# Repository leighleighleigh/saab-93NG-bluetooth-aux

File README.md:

# saab-93NG-bluetooth-aux
A module to augment the Aux-In functionality of SAAB 93NG's (2002/3+), to add Bluetooth media playback and steering wheel media control support.

<blockquote>
<p><b>September 30th 2022 update - PCB ordered!</b></p>

</blockquote>

# Features
 - Bluetooth music playback through the wired AUX port
 - Steering wheel button controls
   - Play / Pause
   - Next / Previous
   - *WIP* Voice Assistant 
   - *WIP* Accept incoming phone call 
 - **[SOON]** Digital Microphone support
 - **[FUTURE]** SID integration for automatic Aux-switching
 - **[FUTURE]** SID augmentation, to show music track names etc.

# Project Layout
- /hardware/saab_bluetooth_aux_kit
  - Version 1 hardware. Very basic, breakout-module-based. KiCAD 5
- /hardware/saab_bluetooth_aux_kit_v2
  - Version 2 of the 'kit'. WeMos LOLIN32-Lite module is used as the MCU. Some SMD components for power supply and CAN. Multiple through-hole DAC options (PCM5102, UDH1334H). KiCAD 6.
- /hardware/esp32_93NG_btaux_v2
  - Version 2 hardware, unfinished. Intention was to use full-SMD components, and have multiple CAN interfaces. Currently too much work, and not as approachable for newbies.
- /esp32_a2dp_reciever
  - PlatformIO project, the software flashed to the ESP32 module.
  - Utilises the Arduino for ESP32 framework.

# Version 1, Prototype
The first edition of the PCB serves only to wire together some off-the-shelf modules, after they were tested on a breadboard.

## Prototype parts
 - ESP32 NodeMCU Board (30-pin variant)
 - Adafruit I2S to Stereo DAC (UDA1334)
 - MCP2515 CAN-bus to SPI interface module

<!-- 
# Notes for building your own (by [jokubasver](https://github.com/jokubasver))
- CAN H connects to LS GMLAN1 (green wire, it can be found on the ICM connector pin 1, or solder directly to ICM connector PCB pad).
- CAN L connects to GND
- Connect a 4.7k resistor between CAN H and CAN L
  - So to make it simple - Since the whole Bluetooth Aux board is getting GND from the AUX connection, I connected GND from the MCP2515 module to CAN L, and I connected a 4.7k resistor across CAN H and CAN L on the MCP2515 module.

- Everything also works if I leave CAN L disconnected and not use the 4.7k resistor. CAN L can be left floating as described here: https://electronics.stackexchange.com/questions/139562/single-wire-can-saab-9-3-i-bus-gmlan#comment670941_139882
  - Question is - which is the proper way? Leave out the terminating resistor and leave CAN L floating? Or connect CAN L to GND and use a 4.7k terminating resistor? Both connection variants seem to work fine.

- Instead of using 12V, the EHU 5V line can be used.
  - It turns off after ~10-15 seconds after locking the car with the remote. 
  - 5V wakes up as soon as you unlock the car.
  - This requires the use of an isolated 5V-5V DC-DC converter (see below)

- 5V, GND, AUX Left, AUX right can be soldered on the EHU PCB. All pads are clearly marked.

- Using EHU 5V will cause some audible Bluetooth interference. 
  - Use an isolated 5V-5V DC-DC converter to eliminate it (CC3-0505SF-E would be pin-compatible and would fit nicely on the bluetooth aux kit PCB)
  - I am personally using AM1SS-0505SJZ together with capacitors and inductors that are shown in the datasheet's example schematic. 

- **Warning on EHU 5V line**
  - I have experienced massive current draw from the battery when using this 5V line previously, while experimenting with a generic Bluetooth Aux module. I tried it again with this project and everything is fine.
  - My guess is that my first experiment had a ground loop, and this either caused current to flow through the ground loop, draining the battery, or it confused the EHU and prevented it to go into sleep.
  - Therefore, I highly suggest you use an isolated DC-DC converter (whether you are using 12V, or 5V from the EHU)
-->

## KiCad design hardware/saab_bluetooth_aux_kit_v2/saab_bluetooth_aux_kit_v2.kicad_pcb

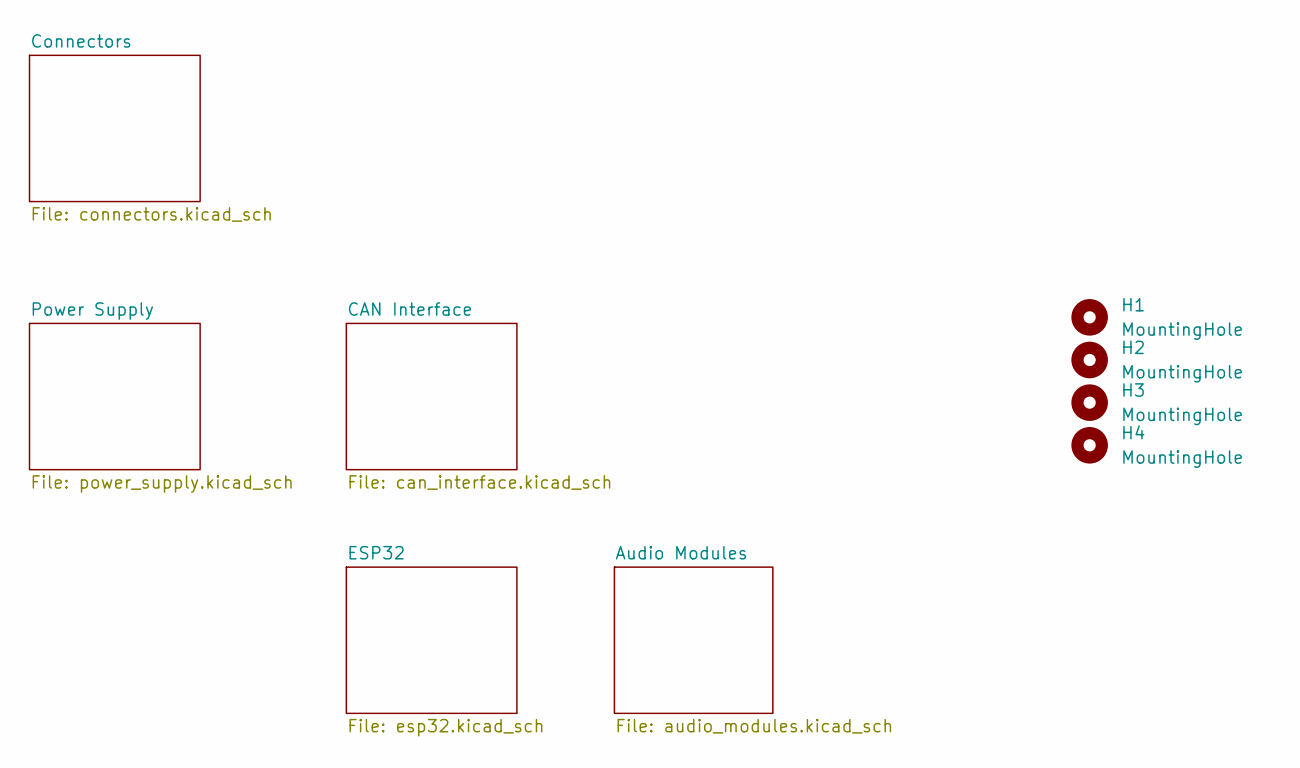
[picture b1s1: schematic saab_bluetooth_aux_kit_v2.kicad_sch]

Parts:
H1, H2, H3, H4: MountingHole; MountingHole_3.2mm_M3_BARE

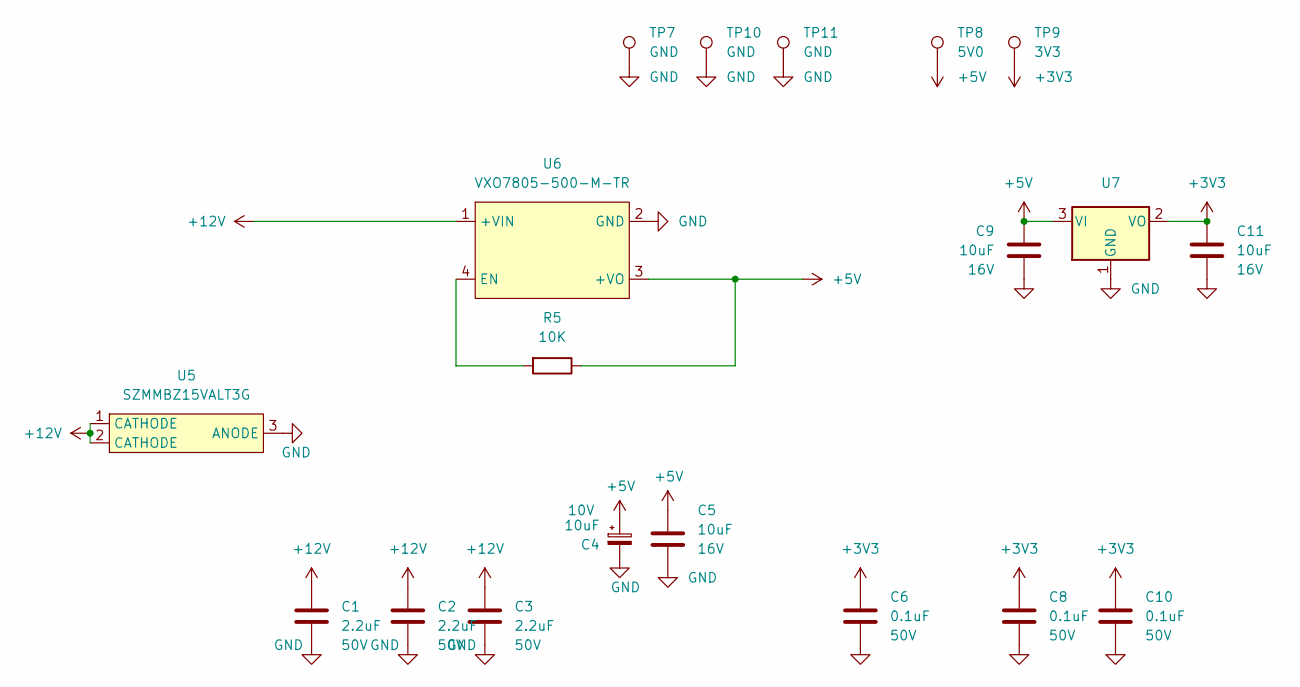
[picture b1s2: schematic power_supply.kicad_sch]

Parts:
C1, C2, C3: 2.2uF; C_0805_2012Metric; Rated Voltage 50V
C4: 10uF; CP_EIA-6032-20_AVX-F; Voltage 10V
C5, C9, C11: 10uF; C_0805_2012Metric; Rated Voltage 16V
C6, C8, C10: 0.1uF; C_0805_2012Metric; Rated Voltage 50V
R5: 10K; R_0805_2012Metric
TP7, TP10, TP11: GND; TestPoint_THTPad_D2.0mm_Drill1.0mm
TP8: 5V0; TestPoint_THTPad_D2.0mm_Drill1.0mm
TP9: 3V3; TestPoint_THTPad_D2.0mm_Drill1.0mm
U5: SZMMBZ15VALT3G; TSOT-23
U6: VXO7805-500-M-TR
U7: NCP1117LPST33T3G; SOT-223-3_TabPin2

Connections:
+3V3: C6.1, C8.1, C10.1, C11.1, TP9.1, U7.2 (VO); also elsewhere on the board
+5V: C4.1, C5.1, C9.1, R5.1, TP8.1, U6.3 (+VO), U7.3 (VI); also elsewhere on the board
+12V: C1.1, C2.1, C3.1, U5.1 (CATHODE), U5.2 (CATHODE), U6.1 (+VIN); also elsewhere on the board
GND: C1.2, C2.2, C3.2, C4.2, C5.2, C6.2, C8.2, C9.2, C10.2, C11.2, TP7.1, TP10.1, TP11.1, U5.3 (ANODE), U6.2 (GND), U7.1 (GND); also elsewhere on the board
unnamed: R5.2, U6.4 (EN)

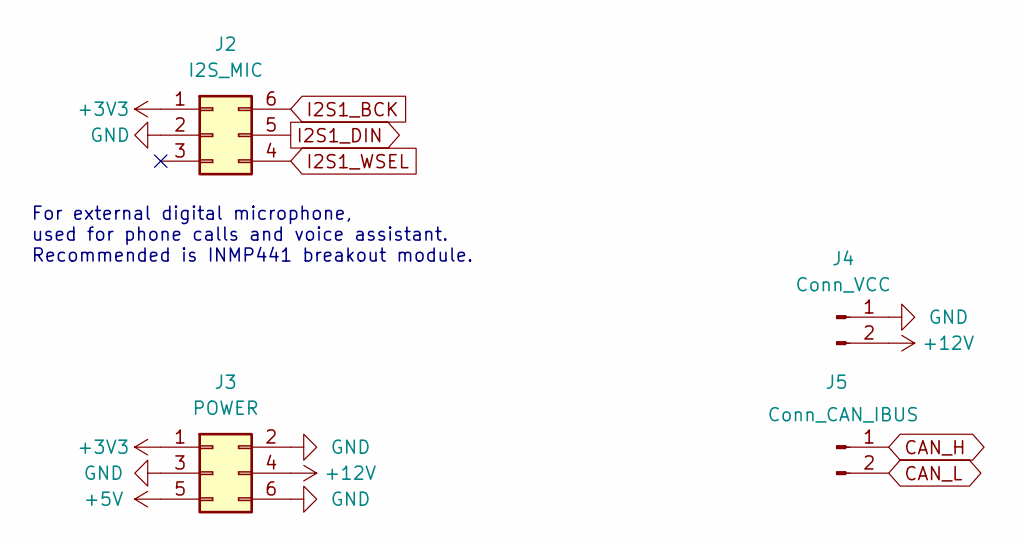
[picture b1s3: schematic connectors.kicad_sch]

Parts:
J2: I2S_MIC; PinHeader_2x03_P2.54mm_Vertical
J3: POWER; PinHeader_2x03_P2.54mm_Vertical
J4: Conn_VCC; Molex_Mega-Fit_76825-0002_2x01_P5.70mm_Horizontal
J5: Conn_CAN_IBUS; Molex_Mega-Fit_76825-0002_2x01_P5.70mm_Horizontal

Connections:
+3V3: J2.1, J3.1; also elsewhere on the board
+5V: J3.5; also elsewhere on the board
+12V: J3.4, J4.2; also elsewhere on the board
CAN_H: J5.1; also elsewhere on the board
CAN_L: J5.2; also elsewhere on the board
GND: J2.2, J3.2, J3.3, J3.6, J4.1; also elsewhere on the board
I2S1_BCK: J2.6; also elsewhere on the board
I2S1_DIN: J2.5; also elsewhere on the board
I2S1_WSEL: J2.4; also elsewhere on the board

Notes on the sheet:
For external digital microphone, used for phone calls and voice assistant. Recommended is INMP441 breakout module.

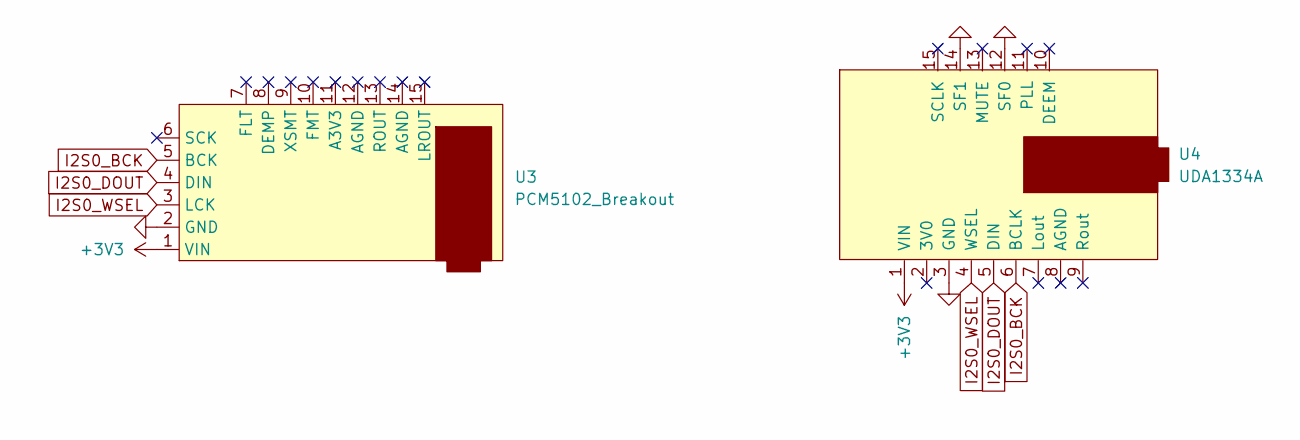
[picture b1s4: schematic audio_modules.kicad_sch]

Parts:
U3: PCM5102_Breakout
U4: UDA1334A; UDA1334_AudioBreakout

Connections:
+3V3: U3.1 (VIN), U4.1 (VIN); also elsewhere on the board
GND: U3.2 (GND), U4.3 (GND), U4.12 (SF0), U4.14 (SF1); also elsewhere on the board
I2S0_BCK: U3.5 (BCK), U4.6 (BCLK); also elsewhere on the board
I2S0_DOUT: U3.4 (DIN), U4.5 (DIN); also elsewhere on the board
I2S0_WSEL: U3.3 (LCK), U4.4 (WSEL); also elsewhere on the board

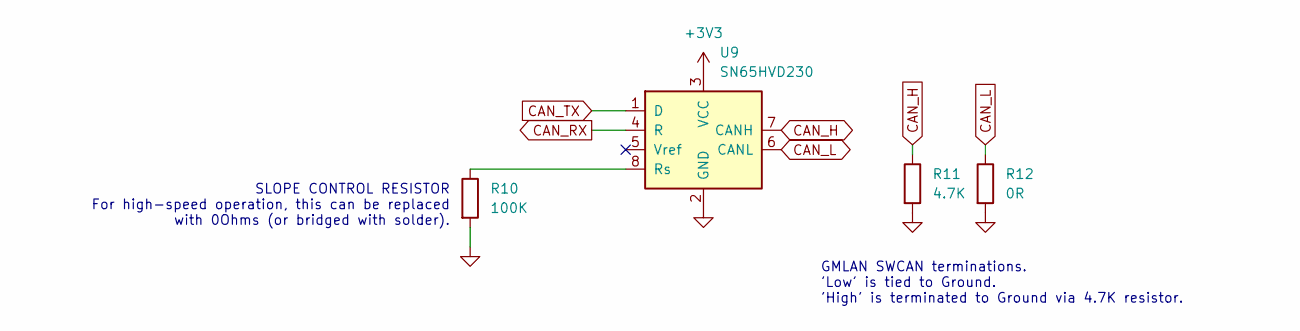
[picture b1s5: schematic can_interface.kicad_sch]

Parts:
R10: 100K; R_0805_2012Metric
R11: 4.7K; R_1206_3216Metric
R12: 0R; R_1206_3216Metric
U9: SN65HVD230; SOIC-8_3.9x4.9mm_P1.27mm

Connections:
+3V3: U9.3 (VCC); also elsewhere on the board
CAN_H: R11.1, U9.7 (CANH); also elsewhere on the board
CAN_L: R12.1, U9.6 (CANL); also elsewhere on the board
CAN_RX: U9.4 (R); also elsewhere on the board
CAN_TX: U9.1 (D); also elsewhere on the board
GND: R10.2, R11.2, R12.2, U9.2 (GND); also elsewhere on the board
unnamed: R10.1, U9.8 (Rs)

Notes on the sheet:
SLOPE CONTROL RESISTOR For high-speed operation, this can be replaced with 0Ohms (or bridged with solder).
GMLAN SWCAN terminations. 'Low' is tied to Ground. 'High' is terminated to Ground via 4.7K resistor.

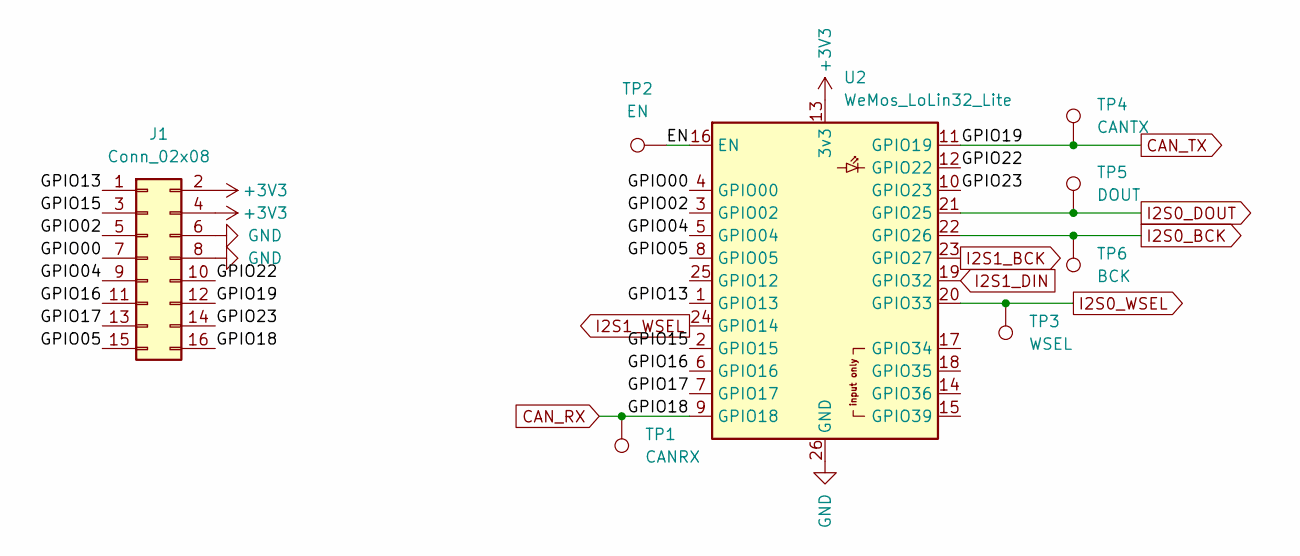
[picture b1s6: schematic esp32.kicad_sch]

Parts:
J1: Conn_02x08; PinHeader_2x08_P2.54mm_Vertical
TP1: CANRX; TestPoint_THTPad_D2.0mm_Drill1.0mm
TP2: EN; TestPoint_THTPad_D2.0mm_Drill1.0mm
TP3: WSEL; TestPoint_THTPad_D2.0mm_Drill1.0mm
TP4: CANTX; TestPoint_THTPad_D2.0mm_Drill1.0mm
TP5: DOUT; TestPoint_THTPad_D2.0mm_Drill1.0mm
TP6: BCK; TestPoint_THTPad_D2.0mm_Drill1.0mm
U2: WeMos_LoLin32_Lite; WEMOS_LoLin32_Lite

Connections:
+3V3: J1.2, J1.4, U2.13 (3v3); also elsewhere on the board
/ESP32/EN: TP2.1, U2.16 (EN)
/ESP32/GPIO00: J1.7, U2.4 (GPIO00)
/ESP32/GPIO02: J1.5, U2.3 (GPIO02)
/ESP32/GPIO04: J1.9, U2.5 (GPIO04)
/ESP32/GPIO05: J1.15, U2.8 (GPIO05)
/ESP32/GPIO13: J1.1, U2.1 (GPIO13)
/ESP32/GPIO15: J1.3, U2.2 (GPIO15)
/ESP32/GPIO16: J1.11, U2.6 (GPIO16)
/ESP32/GPIO17: J1.13, U2.7 (GPIO17)
/ESP32/GPIO22: J1.10, U2.12 (GPIO22)
/ESP32/GPIO23: J1.14, U2.10 (GPIO23)
CAN_RX: J1.16, TP1.1, U2.9 (GPIO18); also elsewhere on the board
CAN_TX: J1.12, TP4.1, U2.11 (GPIO19); also elsewhere on the board
GND: J1.6, J1.8, U2.26 (GND); also elsewhere on the board
I2S0_BCK: TP6.1, U2.22 (GPIO26); also elsewhere on the board
I2S0_DOUT: TP5.1, U2.21 (GPIO25); also elsewhere on the board
I2S0_WSEL: TP3.1, U2.20 (GPIO33); also elsewhere on the board
I2S1_BCK: U2.23 (GPIO27); also elsewhere on the board
I2S1_DIN: U2.19 (GPIO32); also elsewhere on the board
I2S1_WSEL: U2.24 (GPIO14); also elsewhere on the board

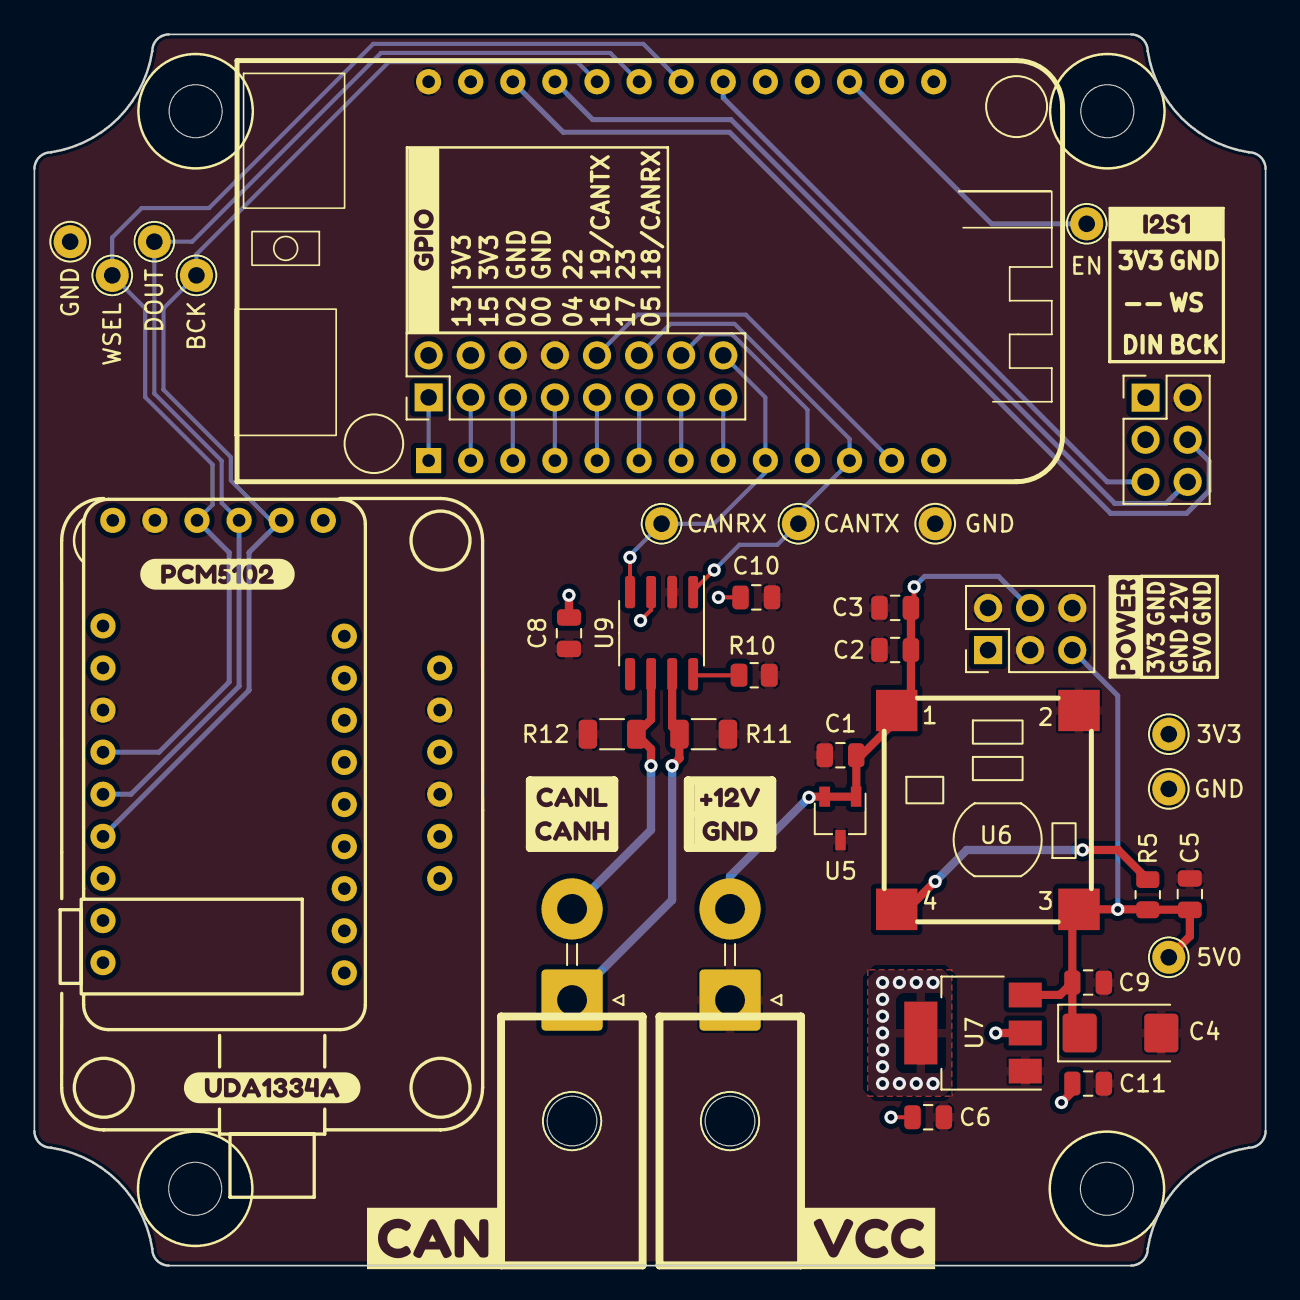
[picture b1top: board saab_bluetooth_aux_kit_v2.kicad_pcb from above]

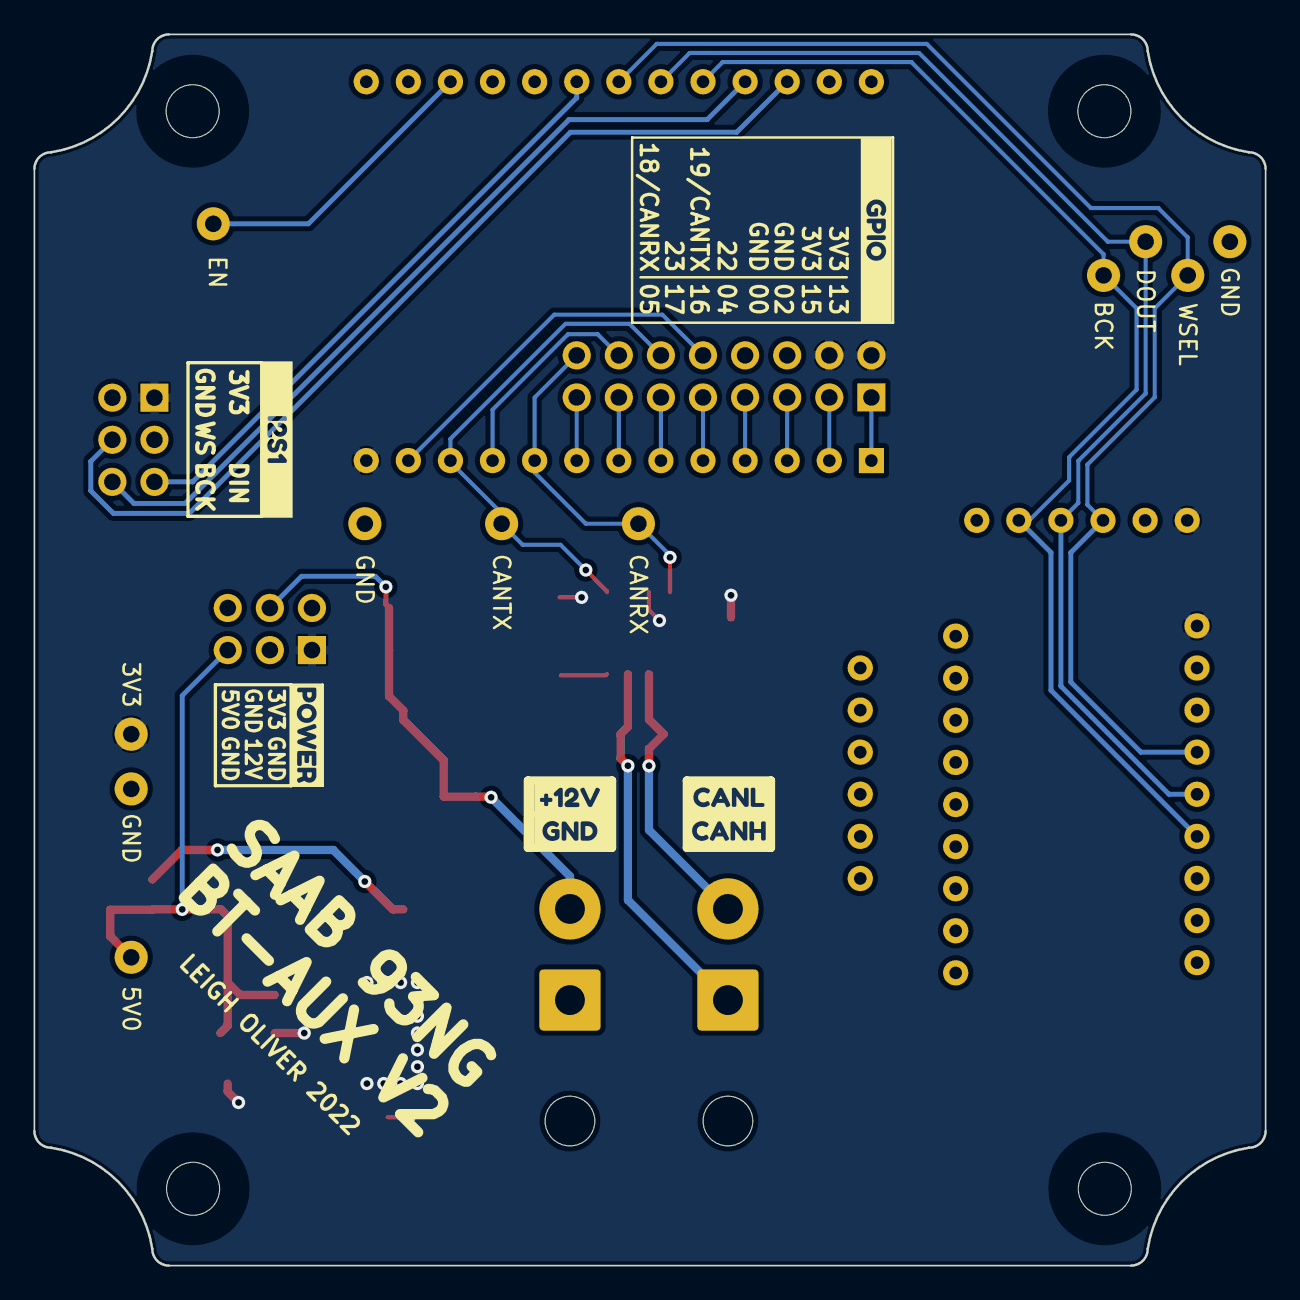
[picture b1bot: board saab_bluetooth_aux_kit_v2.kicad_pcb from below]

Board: 2 copper layers, 74.3 x 74.3 mm, 59 parts (7 on the bottom side), 27 nets.

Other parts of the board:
kibuzzard-62F392E4: G***; kibuzzard-62F392E4
kibuzzard-62F3934B: G***; kibuzzard-62F3934B
kibuzzard-632C5E36: G***; kibuzzard-632C5E36
kibuzzard-632C5EA9: G***; kibuzzard-632C5EA9
kibuzzard-632C5EB0: G***; kibuzzard-632C5EB0
kibuzzard-632C431C, kibuzzard-632C431C#2: G***; kibuzzard-632C431C
kibuzzard-632C4321, kibuzzard-632C4321#2: G***; kibuzzard-632C4321
kibuzzard-632C4325, kibuzzard-632C4325#2: G***; kibuzzard-632C4325
kibuzzard-632C4329, kibuzzard-632C4329#2: G***; kibuzzard-632C4329
kibuzzard-632C7032, kibuzzard-632C7032#2: G***; kibuzzard-632C7032
kibuzzard-632F06BD, kibuzzard-632F06BD#2: G***; kibuzzard-632F06BD
kibuzzard-632F14FF: G***; kibuzzard-632F14FF

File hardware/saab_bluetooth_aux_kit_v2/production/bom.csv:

Designator,Footprint,Quantity,Value,LCSC Part #
TP7,TestPoint_THTPad_D2.0mm_Drill1.0mm,1,GND,
C5,C_0805_2012Metric,1,10uF,
TP9,TestPoint_THTPad_D2.0mm_Drill1.0mm,1,3V3,
TP11,TestPoint_THTPad_D2.0mm_Drill1.0mm,1,GND,
R5,R_0805_2012Metric,1,10K,
R10,R_0805_2012Metric,1,100K,
C10,C_0805_2012Metric,1,0.1uF,
H1,MountingHole_3.2mm_M3_BARE,1,MountingHole,
U6,VXO7805-500-M-TR,1,VXO7805-500-M-TR,
U4,UDA1334_AudioBreakout,1,UDA1334A,
H4,MountingHole_3.2mm_M3_BARE,1,MountingHole,
TP6,TestPoint_THTPad_D2.0mm_Drill1.0mm,1,BCK,
TP10,TestPoint_THTPad_D2.0mm_Drill1.0mm,1,GND,
TP3,TestPoint_THTPad_D2.0mm_Drill1.0mm,1,WSEL,
C4,CP_EIA-6032-20_AVX-F,1,10uF,
TP4,TestPoint_THTPad_D2.0mm_Drill1.0mm,1,CANTX,
TP8,TestPoint_THTPad_D2.0mm_Drill1.0mm,1,5V0,
R12,R_1206_3216Metric,1,0R,
H3,MountingHole_3.2mm_M3_BARE,1,MountingHole,
C8,C_0805_2012Metric,1,0.1uF,
TP5,TestPoint_THTPad_D2.0mm_Drill1.0mm,1,DOUT,
C3,C_0805_2012Metric,1,2.2uF,
U9,SOIC-8_3.9x4.9mm_P1.27mm,1,SN65HVD230,
C1,C_0805_2012Metric,1,2.2uF,
TP2,TestPoint_THTPad_D2.0mm_Drill1.0mm,1,EN,
J3,PinHeader_2x03_P2.54mm_Vertical,1,POWER,
J4,Molex_Mega-Fit_76825-0002_2x01_P5.70mm_Horizontal,1,Conn_VCC,
C11,C_0805_2012Metric,1,10uF,
U3,PCM5102_Breakout,1,PCM5102_Breakout,
TP1,TestPoint_THTPad_D2.0mm_Drill1.0mm,1,CANRX,
H2,MountingHole_3.2mm_M3_BARE,1,MountingHole,
U2,WEMOS_LoLin32_Lite,1,WeMos_LoLin32_Lite,
C6,C_0805_2012Metric,1,0.1uF,
U7,SOT-223-3_TabPin2,1,NCP1117LPST33T3G,
J2,PinHeader_2x03_P2.54mm_Vertical,1,I2S_MIC,
U5,TSOT-23,1,SZMMBZ15VALT3G,
C2,C_0805_2012Metric,1,2.2uF,
R11,R_1206_3216Metric,1,4.7K,
C9,C_0805_2012Metric,1,10uF,
J1,PinHeader_2x08_P2.54mm_Vertical,1,Conn_02x08,
J5,Molex_Mega-Fit_76825-0002_2x01_P5.70mm_Horizontal,1,Conn_CAN_IBUS,

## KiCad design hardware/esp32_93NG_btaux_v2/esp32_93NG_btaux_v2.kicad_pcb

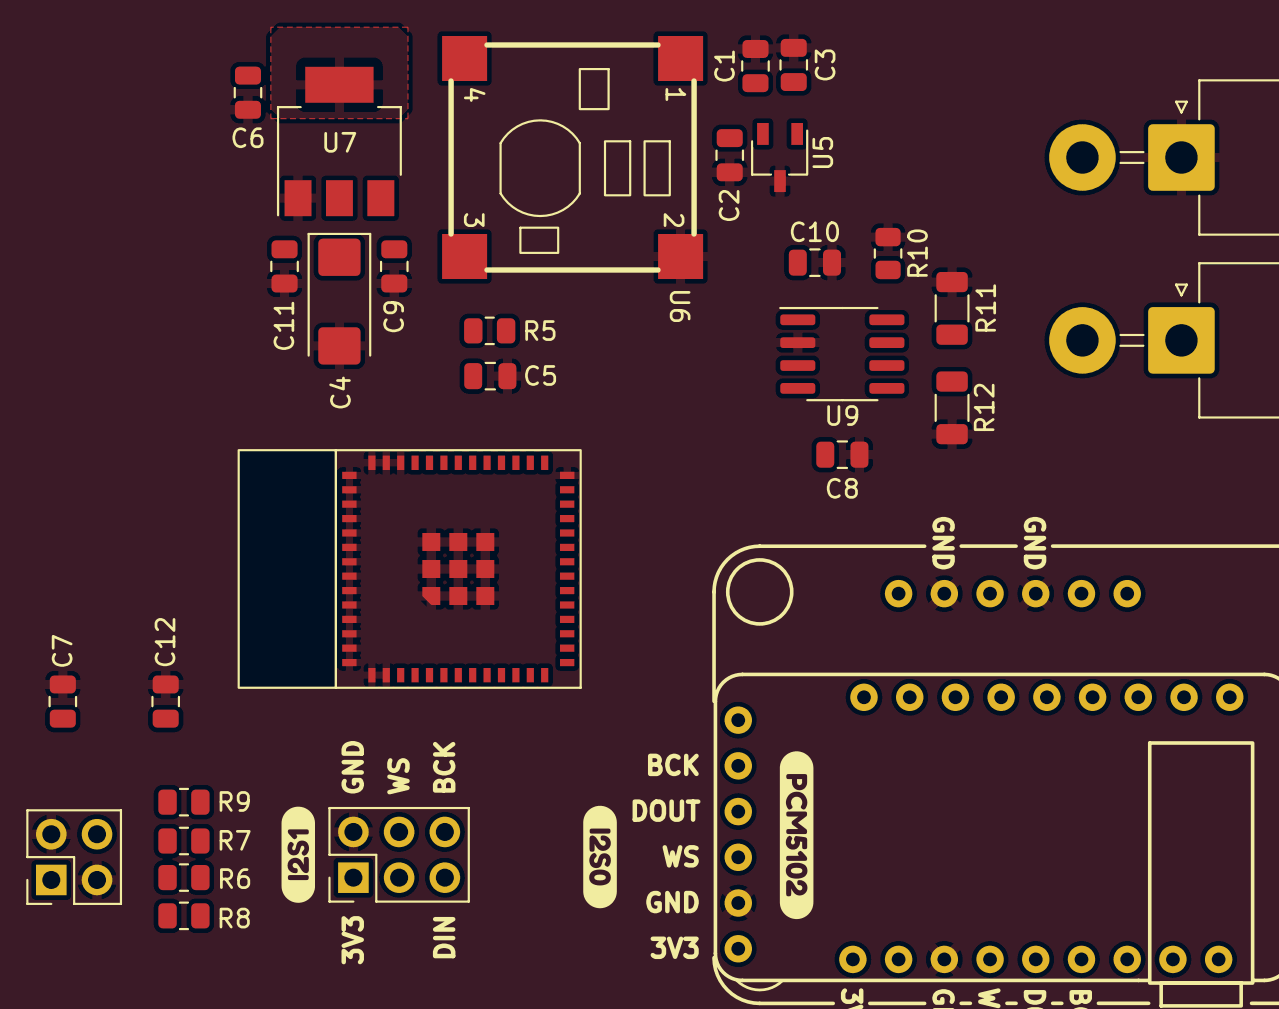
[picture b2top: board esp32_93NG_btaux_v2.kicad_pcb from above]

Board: 2 copper layers, 40 parts (1 on the bottom side), 20 nets, no tracks yet.

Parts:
C1, C2, C3: 2.2uF; C_0805_2012Metric
C4: 10uF; CP_EIA-6032-20_AVX-F
C5, C9, C11, C12: 10uF; C_0805_2012Metric
C6, C7, C8, C10: 0.1uF; C_0805_2012Metric
H1, H2, H3, H4: MountingHole; MountingHole_3.2mm_M3_BARE
J1: SW_EXT; PinHeader_2x02_P2.54mm_Vertical
J2: I2S_MIC; PinHeader_2x03_P2.54mm_Vertical
J4: Conn_VCC; Molex_Mega-Fit_76825-0002_2x01_P5.70mm_Horizontal
J5: Conn_CAN_IBUS; Molex_Mega-Fit_76825-0002_2x01_P5.70mm_Horizontal
R5: 10K; R_0805_2012Metric
R6, R7: 470; R_0805_2012Metric
R8, R9: 10k; R_0805_2012Metric
R10: 100K; R_0805_2012Metric
R11: 4.7K; R_1206_3216Metric
R12: 0R; R_1206_3216Metric
U3: PCM5102_Breakout
U4: UDA1334A; UDA1334_AudioBreakout
U5: SZMMBZ15VALT3G; TSOT-23
U6: VXO7805-500-M-TR
U7: NCP1117LPST33T3G; SOT-223-3_TabPin2
U8: ESP32-MINI-1
U9: SN65HVD230; SOIC-8_3.9x4.9mm_P1.27mm
kibuzzard-62F392E4: G***; kibuzzard-62F392E4
kibuzzard-62F394C5, kibuzzard-62F394C5#2: G***; kibuzzard-62F394C5
kibuzzard-62F395A5: G***; kibuzzard-62F395A5
kibuzzard-62F3934B: G***; kibuzzard-62F3934B

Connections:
+3V3: C6.1, C7.1, C8.1, C10.1, C11.1, C12.1, J2.1, R8.1, R9.1, U3.1 (VIN), U4.1 (VIN), U7.2 (VO), U8.3 (3V3), U9.3 (VCC)
+5V: C4.1, C5.1, C9.1, R5.1, U6.3 (+VO), U7.3 (VI)
+12V: C1.1, C2.1, C3.1, J4.2, U5.1 (CATHODE), U5.2 (CATHODE), U6.1 (+VIN)
/ESP32/BOOT_SW: J1.4, R7.2
/ESP32/EN_SW: J1.1, R6.2
CAN_H: J5.1, R11.1, U9.7 (CANH)
CAN_L: J5.2, R12.1, U9.6 (CANL)
CAN_RX: U8.30 (IO18), U9.4 (R)
CAN_TX: U8.32 (IO19), U9.1 (D)
EN: R6.1, R8.2, U8.8 (EN)
GND: C1.2, C2.2, C3.2, C4.2, C5.2, C6.2, C7.2, C8.2, C9.2, C10.2, C11.2, C12.2, J1.2, J1.3, J2.2, J4.1, R10.2, R11.2, R12.2, U3.2 (GND), U4.3 (GND), U4.12 (SF0), U4.14 (SF1), U5.3 (ANODE), U6.2 (GND), U7.1 (GND), U8.1 (GND), U8.2 (GND), U8.27 (GND), U8.38 (GND), U8.39 (GND), U8.40 (GND), U8.41 (GND), U8.42 (GND), U8.43 (GND), U8.44 (GND), U8.45 (GND), U8.46 (GND), U8.47 (GND), U8.48 (GND), U8.49 (GND), U8.50 (GND), U8.51 (GND), U8.52 (GND), U8.53 (GND), U8.54 (GND), U8.55 (EPAD), U9.2 (GND)
I2S0_BCK: U3.5 (BCK), U4.6 (BCLK), U8.14 (IO26)
I2S0_DOUT: U3.4 (DIN), U4.5 (DIN), U8.13 (IO25)
I2S0_WSEL: U3.3 (LCK), U4.4 (WSEL), U8.12 (IO33)
I2S1_BCK: J2.6, U8.15 (IO27)
I2S1_DIN: J2.5, U8.11 (IO32)
I2S1_WSEL: J2.4, U8.16 (IO14)
IO0: R7.1, R9.2, U8.21 (IO0)
unnamed: R5.2, U6.4 (EN)
unnamed: R10.1, U9.8 (Rs)

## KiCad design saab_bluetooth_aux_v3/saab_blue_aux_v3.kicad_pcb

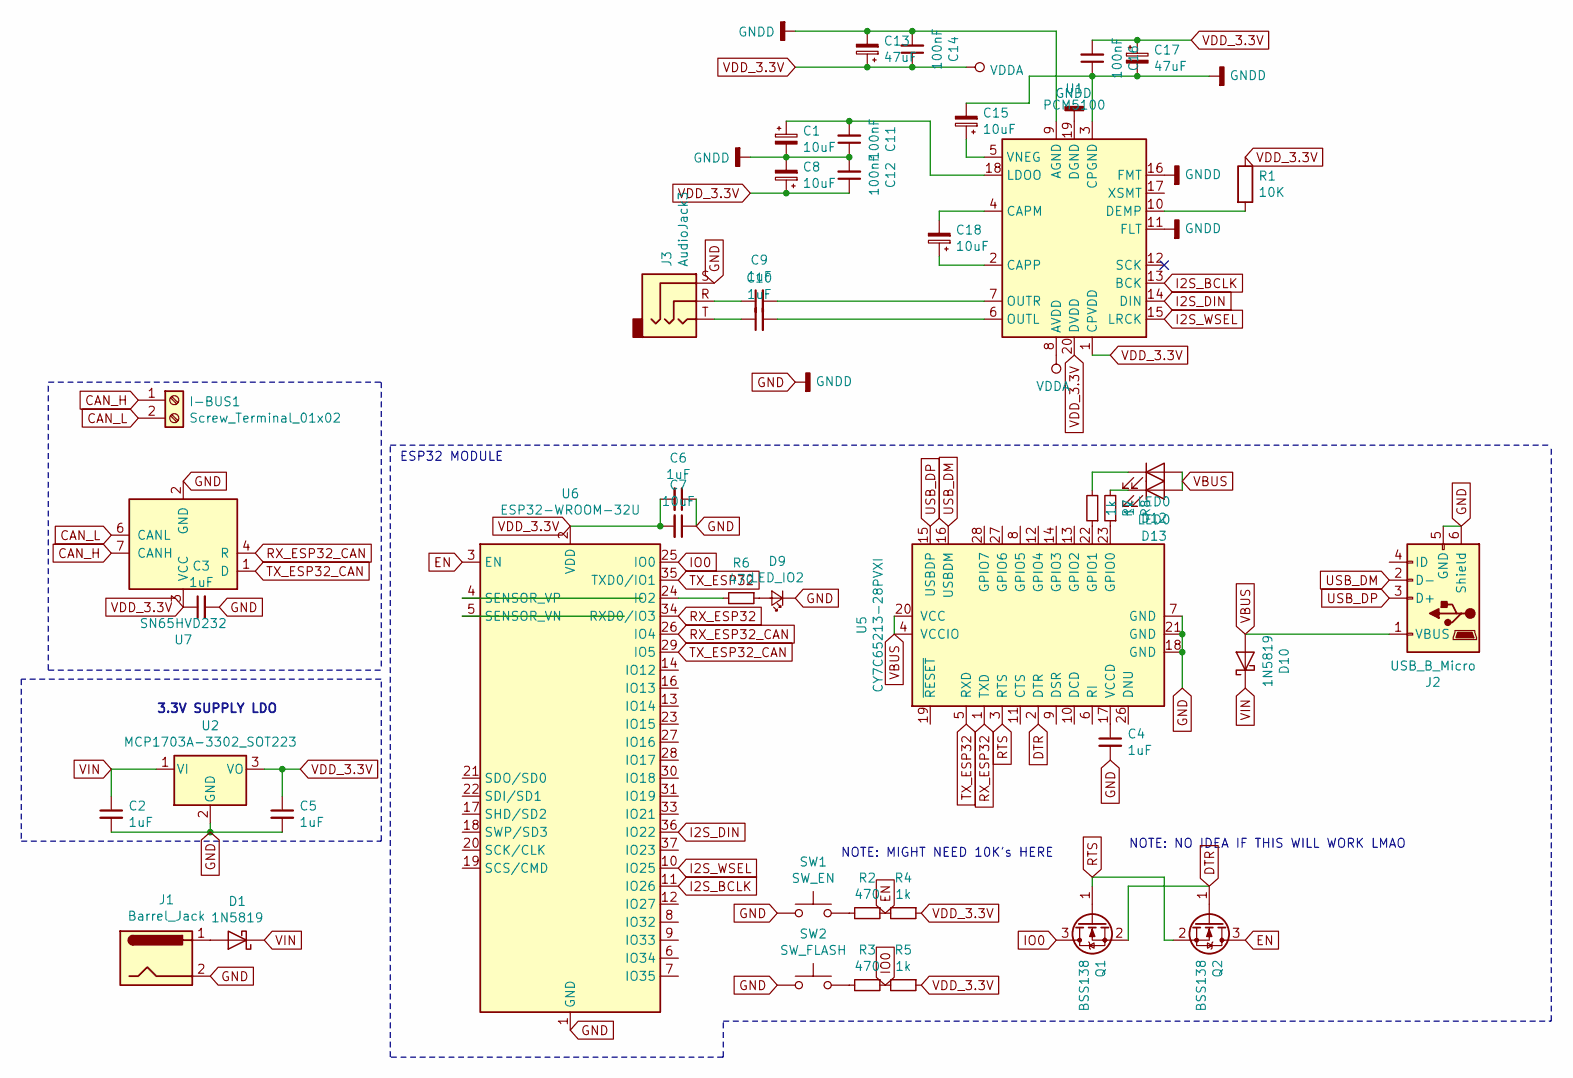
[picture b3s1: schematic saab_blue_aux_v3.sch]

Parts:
C1, C8, C15, C18: 10uF; CP_Elec_4x5.3
C2, C3, C4, C5, C6, C9, C10: 1uF; C_0805_2012Metric_Pad1.15x1.40mm_HandSolder
C7: 10uF; CP_EIA-6032-20_AVX-F_Pad2.25x2.35mm_HandSolder
C11, C12, C14, C16: 100nF; C_0805_2012Metric_Pad1.15x1.40mm_HandSolder
C13, C17: 47uF; CP_Elec_4x5.3
D1, D10: 1N5819; D_SOD-123
D9: LED_IO2; LED_0805_2012Metric_Pad1.15x1.40mm_HandSolder
D12, D13: LED0; LED_0805_2012Metric_Pad1.15x1.40mm_HandSolder
I-BUS1: Screw_Terminal_01x02; TerminalBlock_Phoenix_MKDS-1,5-2-5.08_1x02_P5.08mm_Horizont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
J1: Barrel_Jack; BarrelJack_Wuerth_6941xx301002
J2: USB_B_Micro; USB_Micro-B_Molex-105017-0001
J3: AudioJack3; Jack_3.5mm_CUI_SJ-3523-SMT_Horizontal
Q1, Q2: BSS138; SOT-23
R1: 10K; R_0805_2012Metric_Pad1.15x1.40mm_HandSolder
R2, R3, R6: 470; R_0805_2012Metric_Pad1.15x1.40mm_HandSolder
R4, R5, R7, R8: 1k; R_0805_2012Metric_Pad1.15x1.40mm_HandSolder
SW1: SW_EN; SW_Push_SPST_NO_Alps_SKRK
SW2: SW_FLASH; SW_Push_SPST_NO_Alps_SKRK
U1: PCM5100; TSSOP-20_4.4x6.5mm_P0.65mm
U2: MCP1703A-3302_SOT223; SOT-223-3_TabPin2
U5: CY7C65213-28PVXI; SSOP-28_5.3x10.2mm_P0.65mm
U6: ESP32-WROOM-32U
U7: SN65HVD232; SOIC-8_3.9x4.9mm_P1.27mm

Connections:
CAN_H: I-BUS1.1, U7.7 (CANH)
CAN_L: I-BUS1.2, U7.6 (CANL)
DTR: Q1.2 (S), Q2.1 (G), U5.2 (DTR)
EN: Q2.3 (D), R2.1, R4.2, U6.3 (EN)
GND: C1.2, C2.2, C3.2, C4.2, C5.2, C6.1, C7.1, C8.2, C11.1, C12.2, C13.2, C14.2, C15.2, C16.1, C17.2, D9.1 (K), J1.2, J2.5 (GND), J2.6 (Shield), J3.S, SW1.1, SW2.1, U1.3 (CPGND), U1.9 (AGND), U1.11 (FLT), U1.16 (FMT), U1.19 (DGND), U2.2 (GND), U5.7 (GND), U5.18 (GND), U5.21 (GND), U6.1 (GND), U6.15 (GND), U6.38 (GND), U6.39 (GND), U7.2 (GND)
I2S_BCLK: U1.13 (BCK), U6.11 (IO26)
I2S_DIN: U1.14 (DIN), U6.36 (IO22)
I2S_WSEL: U1.15 (LRCK), U6.10 (IO25)
IO0: Q1.3 (D), R3.1, R5.2, U6.25 (IO0)
unnamed: C1.1, C11.2, U1.18 (LDOO)
unnamed: C4.1, U5.17 (VCCD)
unnamed: C9.1, J3.R
unnamed: C9.2, U1.7 (OUTR)
unnamed: C10.1, J3.T
unnamed: C10.2, U1.6 (OUTL)
unnamed: C15.1, U1.5 (VNEG)
unnamed: C18.1, U1.2 (CAPP)
unnamed: C18.2, U1.4 (CAPM)
unnamed: D1.2 (A), J1.1
unnamed: D9.2 (A), R6.1
unnamed: D12.1 (K), R7.2
unnamed: D13.1 (K), R8.2
unnamed: R1.2, U1.10 (DEMP)
unnamed: R2.2, SW1.2
unnamed: R3.2, SW2.2
unnamed: R6.2, U6.24 (IO2)
unnamed: R7.1, U5.22 (GPIO1)
unnamed: R8.1, U5.23 (GPIO0)
RTS: Q1.1 (G), Q2.2 (S), U5.3 (RTS)
RX_ESP32: U5.1 (TXD), U6.34 (RXD0/IO3)
RX_ESP32_CAN: U6.26 (IO4), U7.4 (R)
TX_ESP32: U5.5 (RXD), U6.35 (TXD0/IO1)
TX_ESP32_CAN: U6.29 (IO5), U7.1 (D)
USB_DM: J2.2 (D-), U5.16 (USBDM)
USB_DP: J2.3 (D+), U5.15 (USBDP)
VBUS: D10.2 (A), D12.2 (A), D13.2 (A), J2.1 (VBUS), U5.4 (VCCIO), U5.20 (VCC)
VDD_3.3V: C3.1, C5.1, C6.2, C7.2, C8.1, C12.1, C13.1, C14.1, C16.2, C17.1, R1.1, R4.1, R5.1, U1.1 (CPVDD), U1.8 (AVDD), U1.20 (DVDD), U2.3 (VO), U6.2 (VDD), U7.3 (VCC)
VIN: C2.1, D1.1 (K), D10.1 (K), U2.1 (VI)

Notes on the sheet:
3.3V SUPPLY LDO
ESP32 MODULE
NOTE: MIGHT NEED 10K's HERE
NOTE: NO IDEA IF THIS WILL WORK LMAO

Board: 2 copper layers, 44 parts (0 on the bottom side), 38 nets, no tracks yet.

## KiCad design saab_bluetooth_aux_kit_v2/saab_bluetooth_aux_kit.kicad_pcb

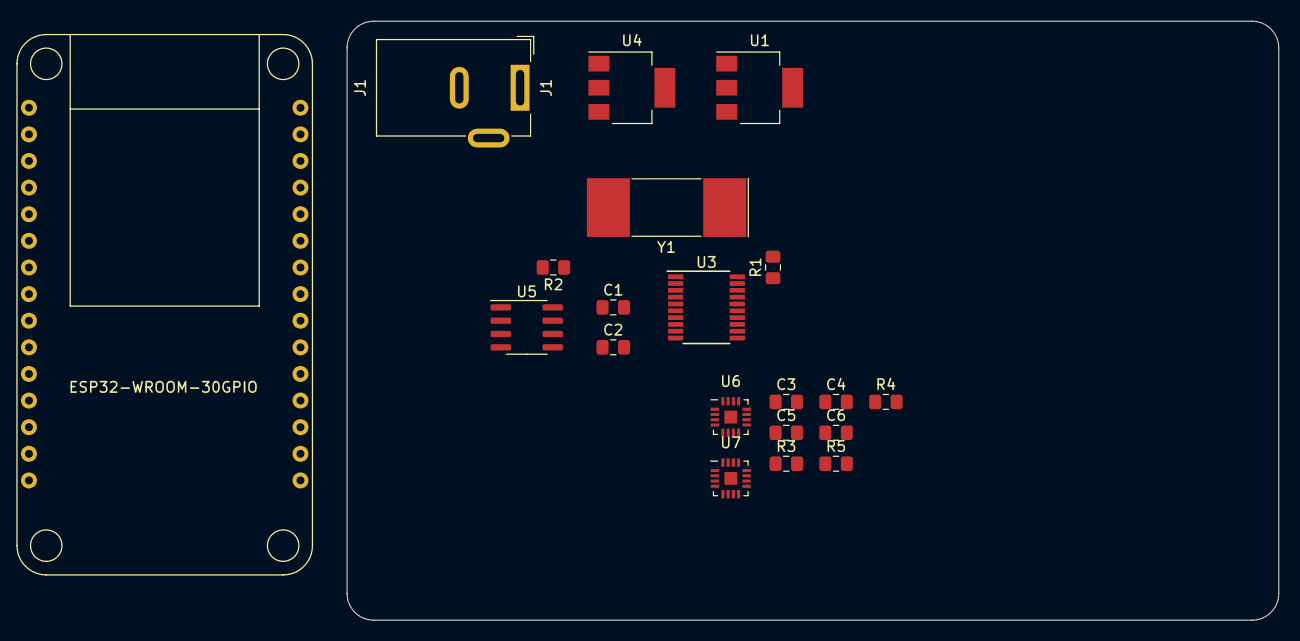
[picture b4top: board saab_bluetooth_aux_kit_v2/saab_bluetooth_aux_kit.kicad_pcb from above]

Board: 2 copper layers, 88.9 x 57.2 mm, 20 parts (0 on the bottom side), 19 nets, no tracks yet.

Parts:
C1, C2: 27pF; C_0805_2012Metric_Pad1.15x1.40mm_HandSolder
C3, C5: 10uF; C_0805_2012Metric_Pad1.15x1.40mm_HandSolder
C4, C6: 0.1uF; C_0805_2012Metric_Pad1.15x1.40mm_HandSolder
J1: Barrel_Jack; BarrelJack_Wuerth_6941xx301002
R1, R2: 10k; R_0805_2012Metric_Pad1.15x1.40mm_HandSolder
R3, R4: 100k; R_0805_2012Metric_Pad1.15x1.40mm_HandSolder
R5: 210.2k; R_0805_2012Metric_Pad1.15x1.40mm_HandSolder
U1: MCP1703A-5002_SOT223; SOT-223-3_TabPin2
U2: ESP32-WROOM-30GPIO
U3: MCP2515-xST; TSSOP-20_4.4x6.5mm_P0.65mm
U4: MCP1703A-3302_SOT223; SOT-223-3_TabPin2
U5: MCP2551-I-P; SOIC-8_3.9x4.9mm_P1.27mm
U6, U7: MAX98357A
Y1: Crystal; Crystal_SMD_SeikoEpson_MA505-2Pin_12.7x5.1mm

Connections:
3.3VDC: C3.1, C4.1, C5.1, C6.1, R4.2, R5.1, U4.3, U6.4, U6.7, U6.8, U7.7, U7.8
5VDC: R1.2, U1.3, U2.VIN, U3.20, U5.3
/Sheet5EEA5C09/GAIN_SEL: R3.2, R4.1, U6.2, U7.2
GND: C1.2, C2.2, C3.2, C4.2, C5.2, C6.2, J1.2, R2.2, R3.1, U1.2, U2.GND, U3.10, U4.2, U5.2, U6.3, U6.11, U6.15, U7.3, U7.11, U7.15
I2S_BCLK: U2.GPIO26, U6.16, U7.16
I2S_DIN: U2.GPIO22, U6.1, U7.1
I2S_WSEL: U2.GPIO25, U6.14, U7.14
unnamed: C1.1, U3.8, Y1.1
unnamed: C2.1, U3.9, Y1.2
unnamed: R1.1, U3.19
unnamed: R2.1, U5.8
unnamed: R5.2, U7.4
unnamed: U3.1, U5.1
unnamed: U3.2, U5.4
SPI_CS: U2.GPIO5, U3.18
SPI_MISO: U2.GPIO19, U3.17
SPI_MOSI: U2.GPIO23, U3.16
SPI_SCLK: U2.GPIO18, U3.14
VIN_12V: J1.1, U1.1, U4.1

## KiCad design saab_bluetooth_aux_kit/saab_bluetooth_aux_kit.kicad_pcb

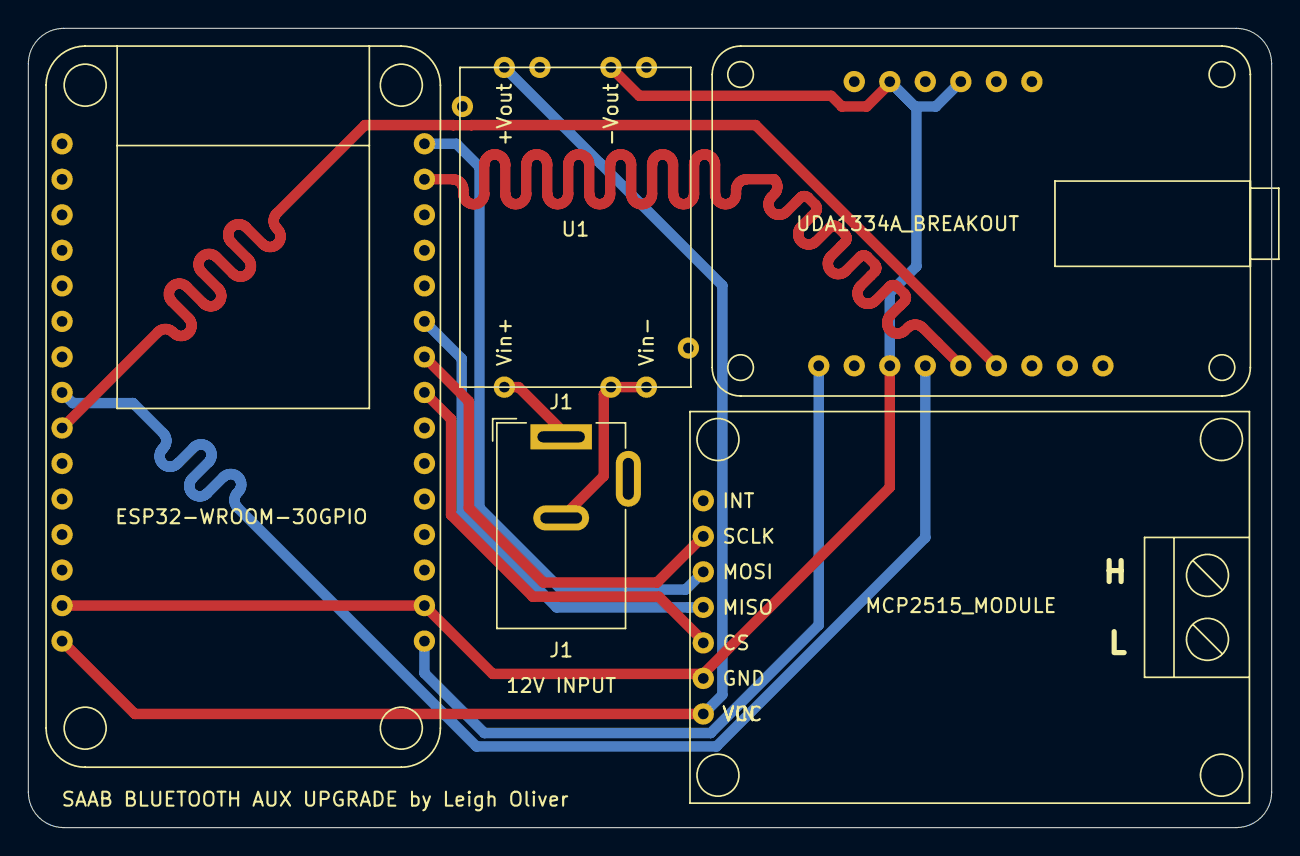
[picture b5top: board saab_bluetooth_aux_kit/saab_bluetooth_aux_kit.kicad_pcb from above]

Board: 2 copper layers, 88.9 x 57.2 mm, 5 parts (0 on the bottom side), 12 nets.

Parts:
J1: Barrel_Jack; BarrelJack_Wuerth_6941xx301002
U1: CC3-1205SF-E
U2: ESP32-WROOM-30GPIO
U3: MCP2515_MODULE; MCP2515_Module
U4: UDA1334A_BREAKOUT; UDA1334A-Breakout

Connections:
3VDC: U2.3V3, U4.VIN
5VDC: U1.7, U2.VIN, U3.VIN
GND: U1.5, U2.GND, U3.GND, U4.GND, U4.SF0, U4.SF1
I2S_BCLK: U2.GPIO26, U4.BCLK
I2S_DIN: U2.GPIO22, U4.DIN
I2S_WSEL: U2.GPIO25, U4.WSEL
unnamed: J1.1, U1.1
unnamed: J1.2, U1.2, U1.3
SPI_CS: U2.GPIO5, U3.CS
SPI_MISO: U2.GPIO19, U3.MISO
SPI_MOSI: U2.GPIO23, U3.MOSI
SPI_SCLK: U2.GPIO18, U3.SCLK
